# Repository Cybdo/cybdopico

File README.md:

# Cybdo Pico!
RP 2040 based devboard, inspired by the Raspberry Pi Pico and the Orpheus Pico

## Key Features
- RP2040 microcontroller with 16Mibit (2MB) flash
- Raspberry Pi Pico form factor compatiable
- USB-C connectivity
- Dedicated Reset switch
- PCB Touch button (GPIO24)
- All 0603 components where applicable for easier hand soldering
- Pin labels on both sides
- Exposed GPIO29 pin
- Hack Club art :)

## Schematics

## Board

## JLC order

## Firmware
Compatiable with most Pi Pico firmwares, including [MicroPython](https://micropython.org/) and [CircuitPython](https://circuitpython.org/)

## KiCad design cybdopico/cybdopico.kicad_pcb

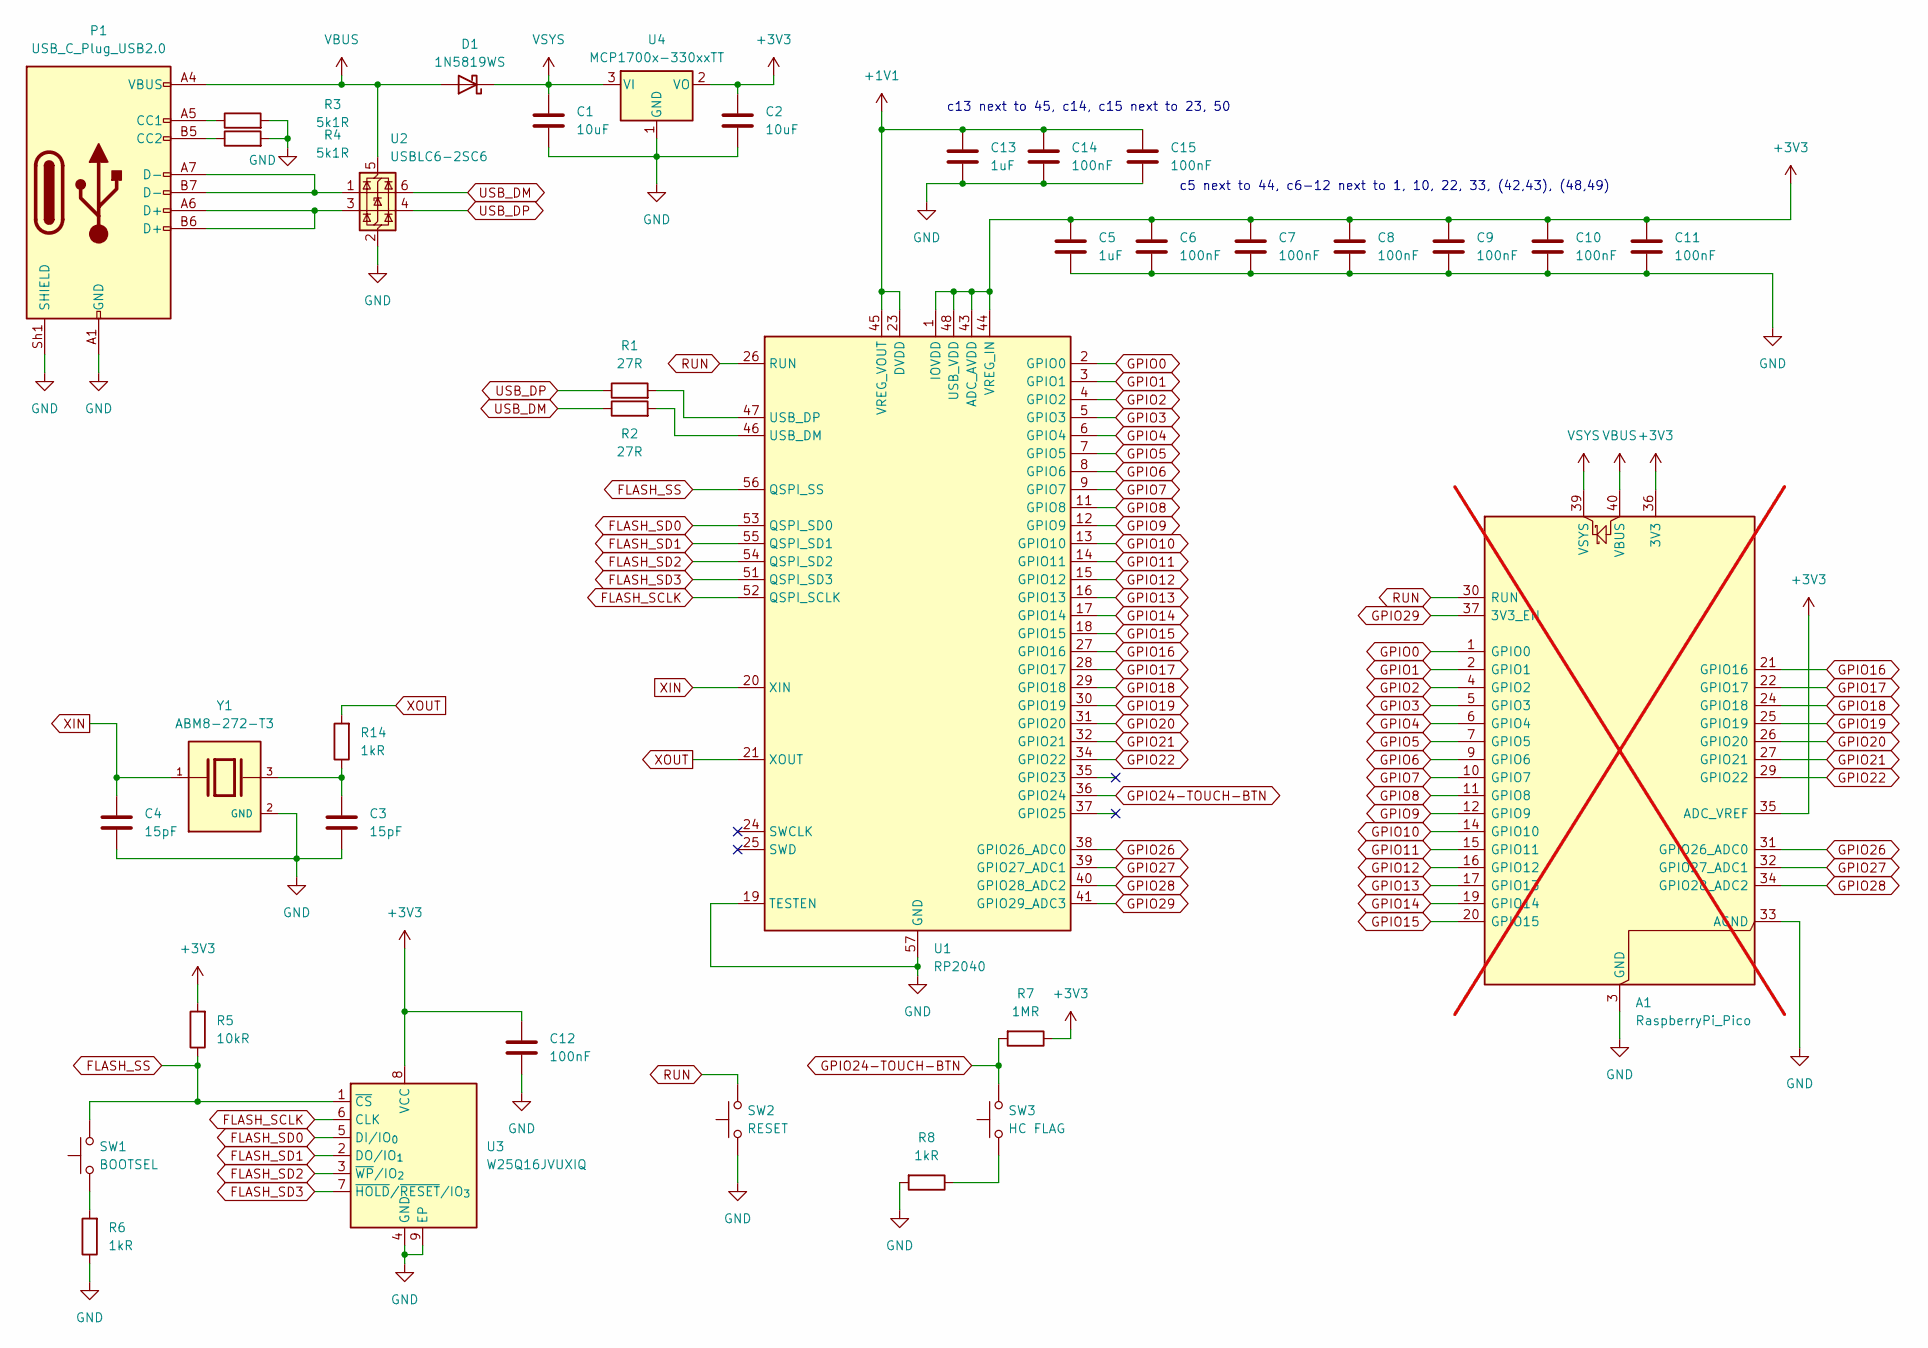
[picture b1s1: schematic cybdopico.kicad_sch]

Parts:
A1: RaspberryPi_Pico; RaspberryPi_Pico_Common_Unspecified; not fitted
C1, C2: 10uF; C_0603_1608Metric_Pad1.08x0.95mm_HandSolder
C3, C4: 15pF; C_0603_1608Metric_Pad1.08x0.95mm_HandSolder
C5, C13: 1uF; C_0603_1608Metric_Pad1.08x0.95mm_HandSolder
C6, C7, C8, C9, C10, C11, C12, C14, C15: 100nF; C_0603_1608Metric_Pad1.08x0.95mm_HandSolder
D1: 1N5819WS; D_SOD-323
P1: USB_C_Plug_USB2.0; TYPE-C-31-M-12
R1, R2: 27R; R_0603_1608Metric_Pad0.98x0.95mm_HandSolder
R3, R4: 5k1R; R_0603_1608Metric_Pad0.98x0.95mm_HandSolder
R5: 10kR; R_0603_1608Metric_Pad0.98x0.95mm_HandSolder
R6: 1kR; R_0603_1608Metric_Pad0.98x0.95mm_HandSolder
R7: 1MR; R_0603_1608Metric
R8, R14: 1kR; R_0603_1608Metric
SW1: BOOTSEL; SW_Push_SPST_NO_Alps_SKRK
SW2: RESET; SW_Push_SPST_NO_Alps_SKRK
SW3: HC FLAG; hackclub flag touch
U1: RP2040; QFN-56-1EP_7x7mm_P0.4mm_EP3.2x3.2mm
U2: USBLC6-2SC6; SOT-23-6
U3: W25Q16JVUXIQ; Winbond_USON-8-1EP_3x2mm_P0.5mm_EP0.2x1.6mm
U4: MCP1700x-330xxTT; SOT-23
Y1: ABM8-272-T3; Crystal_SMD_Abracon_ABM8G-4Pin_3.2x2.5mm; PARTREV 07-29-20

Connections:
+1V1: C13.1, C14.1, C15.1, U1.23 (DVDD), U1.45 (VREG_VOUT), U1.50 (DVDD)
+3V3: A1.35 (ADC_VREF), A1.36 (3V3), C2.1, C5.1, C6.1, C7.1, C8.1, C9.1, C10.1, C11.1, C12.1, R5.2, R7.1, U1.1 (IOVDD), U1.10 (IOVDD), U1.22 (IOVDD), U1.33 (IOVDD), U1.42 (IOVDD), U1.43 (ADC_AVDD), U1.44 (VREG_IN), U1.48 (USB_VDD), U1.49 (IOVDD), U3.8 (VCC), U4.2 (VO)
FLASH_SCLK: U1.52 (QSPI_SCLK), U3.6 (CLK)
FLASH_SD0: U1.53 (QSPI_SD0), U3.5 (DI/IO_{0})
FLASH_SD1: U1.55 (QSPI_SD1), U3.2 (DO/IO_{1})
FLASH_SD2: U1.54 (QSPI_SD2), U3.3 (~WP/IO_{2})
FLASH_SD3: U1.51 (QSPI_SD3), U3.7 (~HOLD/~RESET/IO_{3})
FLASH_SS: R5.1, SW1.2, U1.56 (QSPI_SS), U3.1 (~CS)
GND: A1.3 (GND), A1.8 (GND), A1.13 (GND), A1.18 (GND), A1.23 (GND), A1.28 (GND), A1.33 (AGND), A1.38 (GND), C1.2, C2.2, C3.2, C4.2, C5.2, C6.2, C7.2, C8.2, C9.2, C10.2, C11.2, C12.2, C13.2, C14.2, C15.2, P1.A1 (GND), P1.A12 (GND), P1.B1 (GND), P1.B12 (GND), P1.Sh1 (SHIELD), R3.2, R4.2, R6.1, R8.2, SW2.1, U1.19 (TESTEN), U1.57 (GND), U2.2 (GND), U3.4 (GND), U3.9 (EP), U4.1 (GND), Y1.2 (GND), Y1.4 (GND)
GPIO0: A1.1 (GPIO0), U1.2 (GPIO0)
GPIO1: A1.2 (GPIO1), U1.3 (GPIO1)
GPIO2: A1.4 (GPIO2), U1.4 (GPIO2)
GPIO3: A1.5 (GPIO3), U1.5 (GPIO3)
GPIO4: A1.6 (GPIO4), U1.6 (GPIO4)
GPIO5: A1.7 (GPIO5), U1.7 (GPIO5)
GPIO6: A1.9 (GPIO6), U1.8 (GPIO6)
GPIO7: A1.10 (GPIO7), U1.9 (GPIO7)
GPIO8: A1.11 (GPIO8), U1.11 (GPIO8)
GPIO9: A1.12 (GPIO9), U1.12 (GPIO9)
GPIO10: A1.14 (GPIO10), U1.13 (GPIO10)
GPIO11: A1.15 (GPIO11), U1.14 (GPIO11)
GPIO12: A1.16 (GPIO12), U1.15 (GPIO12)
GPIO13: A1.17 (GPIO13), U1.16 (GPIO13)
GPIO14: A1.19 (GPIO14), U1.17 (GPIO14)
GPIO15: A1.20 (GPIO15), U1.18 (GPIO15)
GPIO16: A1.21 (GPIO16), U1.27 (GPIO16)
GPIO17: A1.22 (GPIO17), U1.28 (GPIO17)
GPIO18: A1.24 (GPIO18), U1.29 (GPIO18)
GPIO19: A1.25 (GPIO19), U1.30 (GPIO19)
GPIO20: A1.26 (GPIO20), U1.31 (GPIO20)
GPIO21: A1.27 (GPIO21), U1.32 (GPIO21)
GPIO22: A1.29 (GPIO22), U1.34 (GPIO22)
GPIO24-TOUCH-BTN: R7.2, SW3.2, U1.36 (GPIO24)
GPIO26: A1.31 (GPIO26_ADC0), U1.38 (GPIO26_ADC0)
GPIO27: A1.32 (GPIO27_ADC1), U1.39 (GPIO27_ADC1)
GPIO28: A1.34 (GPIO28_ADC2), U1.40 (GPIO28_ADC2)
GPIO29: A1.37 (3V3_EN), U1.41 (GPIO29_ADC3)
unnamed: C3.1, R14.1, Y1.3
unnamed: P1.A5 (CC1), R3.1
unnamed: P1.B5 (CC2), R4.1
unnamed: P1.A6 (D+), P1.B6 (D+), U2.3 (I/O2)
unnamed: P1.A7 (D-), P1.B7 (D-), U2.1 (I/O1)
unnamed: R6.2, SW1.1
unnamed: R8.1, SW3.1
unnamed: R2.2, U1.46 (USB_DM)
unnamed: R1.2, U1.47 (USB_DP)
RUN: A1.30 (RUN), SW2.2, U1.26 (RUN)
USB_DM: R2.1, U2.6 (I/O1)
USB_DP: R1.1, U2.4 (I/O2)
VBUS: A1.40 (VBUS), D1.2 (A), P1.A4 (VBUS), P1.A9 (VBUS), P1.B4 (VBUS), P1.B9 (VBUS), U2.5 (VBUS)
VSYS: A1.39 (VSYS), C1.1, D1.1 (K), U4.3 (VI)
XIN: C4.1, U1.20 (XIN), Y1.1
XOUT: R14.2, U1.21 (XOUT)

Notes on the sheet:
c5 next to 44, c6-12 next to 1, 10, 22, 33, (42,43), (48,49)
c13 next to 45, c14, c15 next to 23, 50

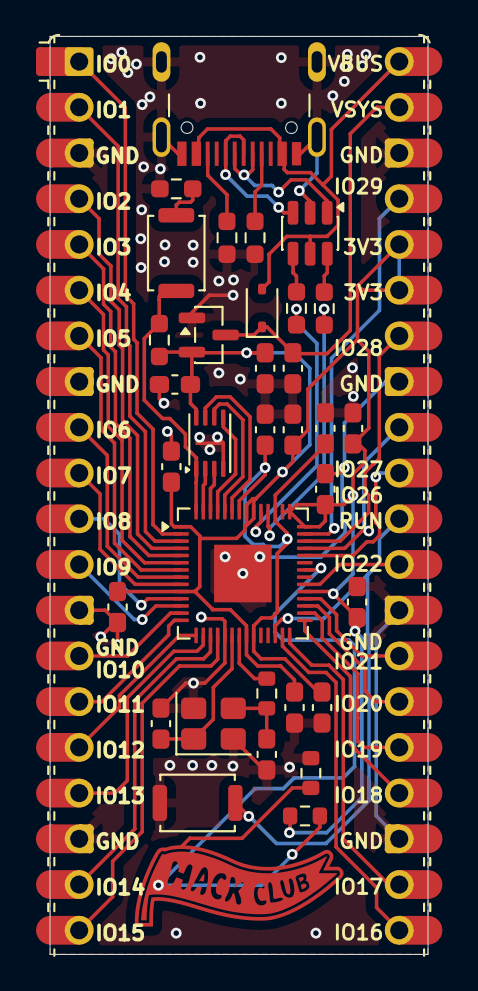
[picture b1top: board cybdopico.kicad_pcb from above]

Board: 2 copper layers, 21.0 x 51.0 mm, 35 parts (0 on the bottom side), 53 nets.

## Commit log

2025-12-23 journal 1
    its 11pm but i wanted to get started anyway
    im gonna try and speedrun this all tomorrow since i dont really have much time after that.
    this is my 3rd time designing a rp2040 minimum system so it should be good...
    anyways laid out the footprint and mcu and connected gpio
2025-12-28 finished everything
2025-12-28 formatting
2025-12-28 update schematic
2025-12-28 fixed resistors and clearned up board (extra vias, traces, etc)
2026-02-08 Rename cybdopico-journal.md to JOURNAL.md
2026-02-08 Rename image.png to cover image.png
2026-02-08 Rename cover image.png to Cover Image.png
2026-04-23 made production files
